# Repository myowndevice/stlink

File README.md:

Данный репозитарий содержит информацию по прибору ST Link

Если вы будете скачивать файлы через web не забудьте скачать общую папку Kicadlib.

[Подробная инструкция как самостоятельно сделать ST-link](http://myowndevice.ru/index.php/pribory/item/16-st-link-v2).

Если вы здесь в прервые посетите [сайт myowndevice.ru](http://myowndevice.ru), там вы найдете более подробную информацию!

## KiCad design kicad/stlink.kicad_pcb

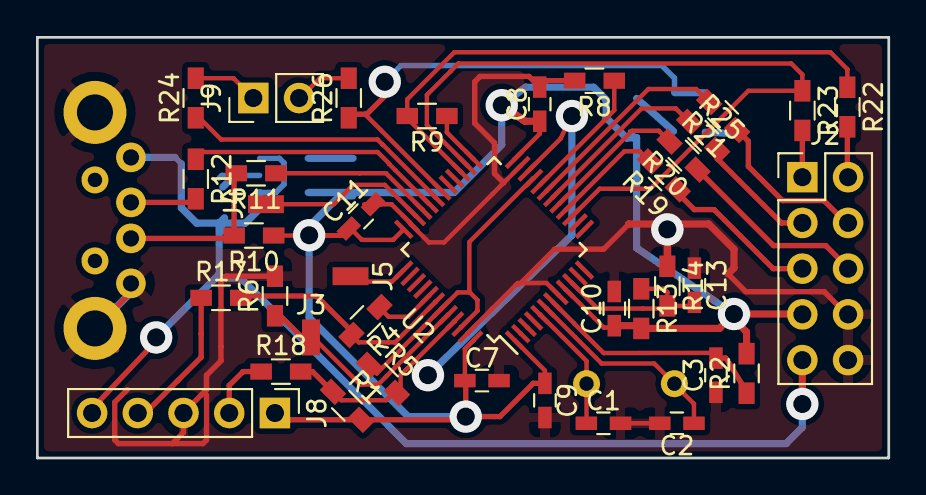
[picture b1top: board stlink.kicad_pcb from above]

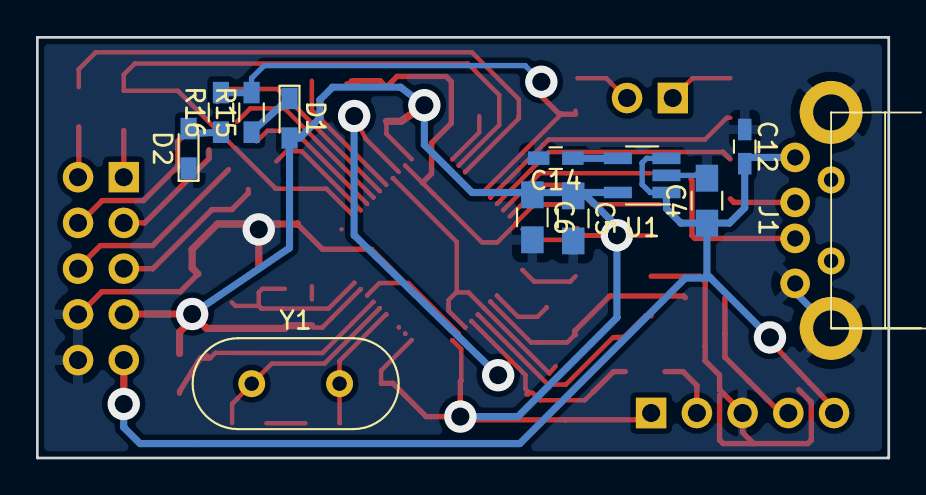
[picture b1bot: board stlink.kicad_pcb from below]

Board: 2 copper layers, 47.3 x 23.4 mm, 50 parts (12 on the bottom side), 41 nets.

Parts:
C1, C2: 22pf; C_0603_HandSoldering
C3, C7, C8, C9, C10, C11, C12, C13: 100n; C_0603_HandSoldering
C4, C5, C6: 10uf; C_0805_HandSoldering
C14: 10n; C_0603_HandSoldering
D1, D2: LED; LED_0603_HandSoldering
J1: USB_A; USB_A_male
J2: jtag; Pin_Header_Straight_2x05_Pitch2.54mm
J3: boot0; wirepad_mini
J4: st_swdio; wirepad_mini
J5: st_swclk; wirepad_mini
J8: SWIM; Pin_Header_Straight_1x05_Pitch2.54mm
J9: st_prog; Pin_Header_Straight_1x02_Pitch2.54mm
R1: 680; R_0603_HandSoldering
R2, R6, R8: 100k; R_0603_HandSoldering
R4, R5, R9: 220; R_0603_HandSoldering
R10: 1k5; R_0603_HandSoldering
R11, R12, R17, R18, R19, R20, R21, R22, R23, R24, R25, R26: 22; R_0603_HandSoldering
R13, R14: 4k7; R_0603_HandSoldering
R15, R16: 1k; R_0603_HandSoldering
U1: LDS3985M33R (NCP603); SOT-23-5_HandSoldering
U2: STM32F103C8Tx; LQFP-48_7x7mm_Pitch0.5mm
Y1: 8mgh; Crystal_HC49-4H_Vertical

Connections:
/5v: C4.1, C12.2, J1.1, J2.9, J8.5, U1.1, U1.3
/PROG_RX: J9.1, R24.2
/PROG_TX: J9.2, R26.2
/RSwim_res: J8.4, R17.1
/Rjrst: J2.4, R21.1
/Rnrst: J2.3, R25.2
/Rswclk: J2.1, R23.2
/Rswdio: J2.2, R22.2
/Rswim: J8.2, R18.1
/Rtdi: J2.6, R20.1
/Rtdo: J2.5, R19.1
/boot0: J3.1, R6.1, U2.44
/dm: R12.1, U2.32
/dp: R11.1, U2.33
/jrst: R21.2, U2.19
/led: R15.2, R16.2, R26.1, U2.30
/nrst: R25.1, U2.18
/rx: R24.1, U2.31
/swim: R1.1, R5.2, R18.2, U2.22, U2.45
/swim_in: R5.1, U2.21, U2.43, U2.46
/swim_reset: R4.2, R17.2, U2.42
/tck_swclk: R23.1, U2.15, U2.26
/tdi: R20.2, U2.17
/tdo: R19.2, U2.16
/tms_swdio: R9.2, R22.1, U2.27
GND: C1.2, C2.2, C3.1, C4.2, C5.2, C6.2, C7.2, C8.2, C9.2, C10.2, C11.2, C12.1, C13.1, C14.2, D2.1, J1.4, J1.5, J2.8, J2.10, J8.3, R6.2, R8.2, R14.1, U1.2, U2.8, U2.23, U2.35, U2.47
unnamed: C1.1, U2.5, Y1.2
unnamed: C2.1, U2.6, Y1.1
unnamed: C3.2, R2.1, U2.7
unnamed: C13.2, R13.1, R14.2, U2.10
unnamed: C14.1, U1.4
unnamed: D1.1, R15.1
unnamed: D2.2, R16.1
unnamed: J1.2, R12.2
unnamed: J1.3, R10.2, R11.2
unnamed: J4.1, U2.34
unnamed: J5.1, U2.37
unnamed: R4.1, U2.41
unnamed: R8.1, U2.20
unnamed: R9.1, U2.25
VDD: C5.1, C6.1, C7.1, C8.1, C9.1, C10.1, C11.1, D1.2, J2.7, J8.1, R1.2, R2.2, R10.1, R13.2, U1.5, U2.9, U2.24, U2.36, U2.48

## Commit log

2017-09-20 start
